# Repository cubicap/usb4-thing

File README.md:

# USB4 Thing

An attemt at creating a USB4 multiplexer controlled by ESP32-S3.

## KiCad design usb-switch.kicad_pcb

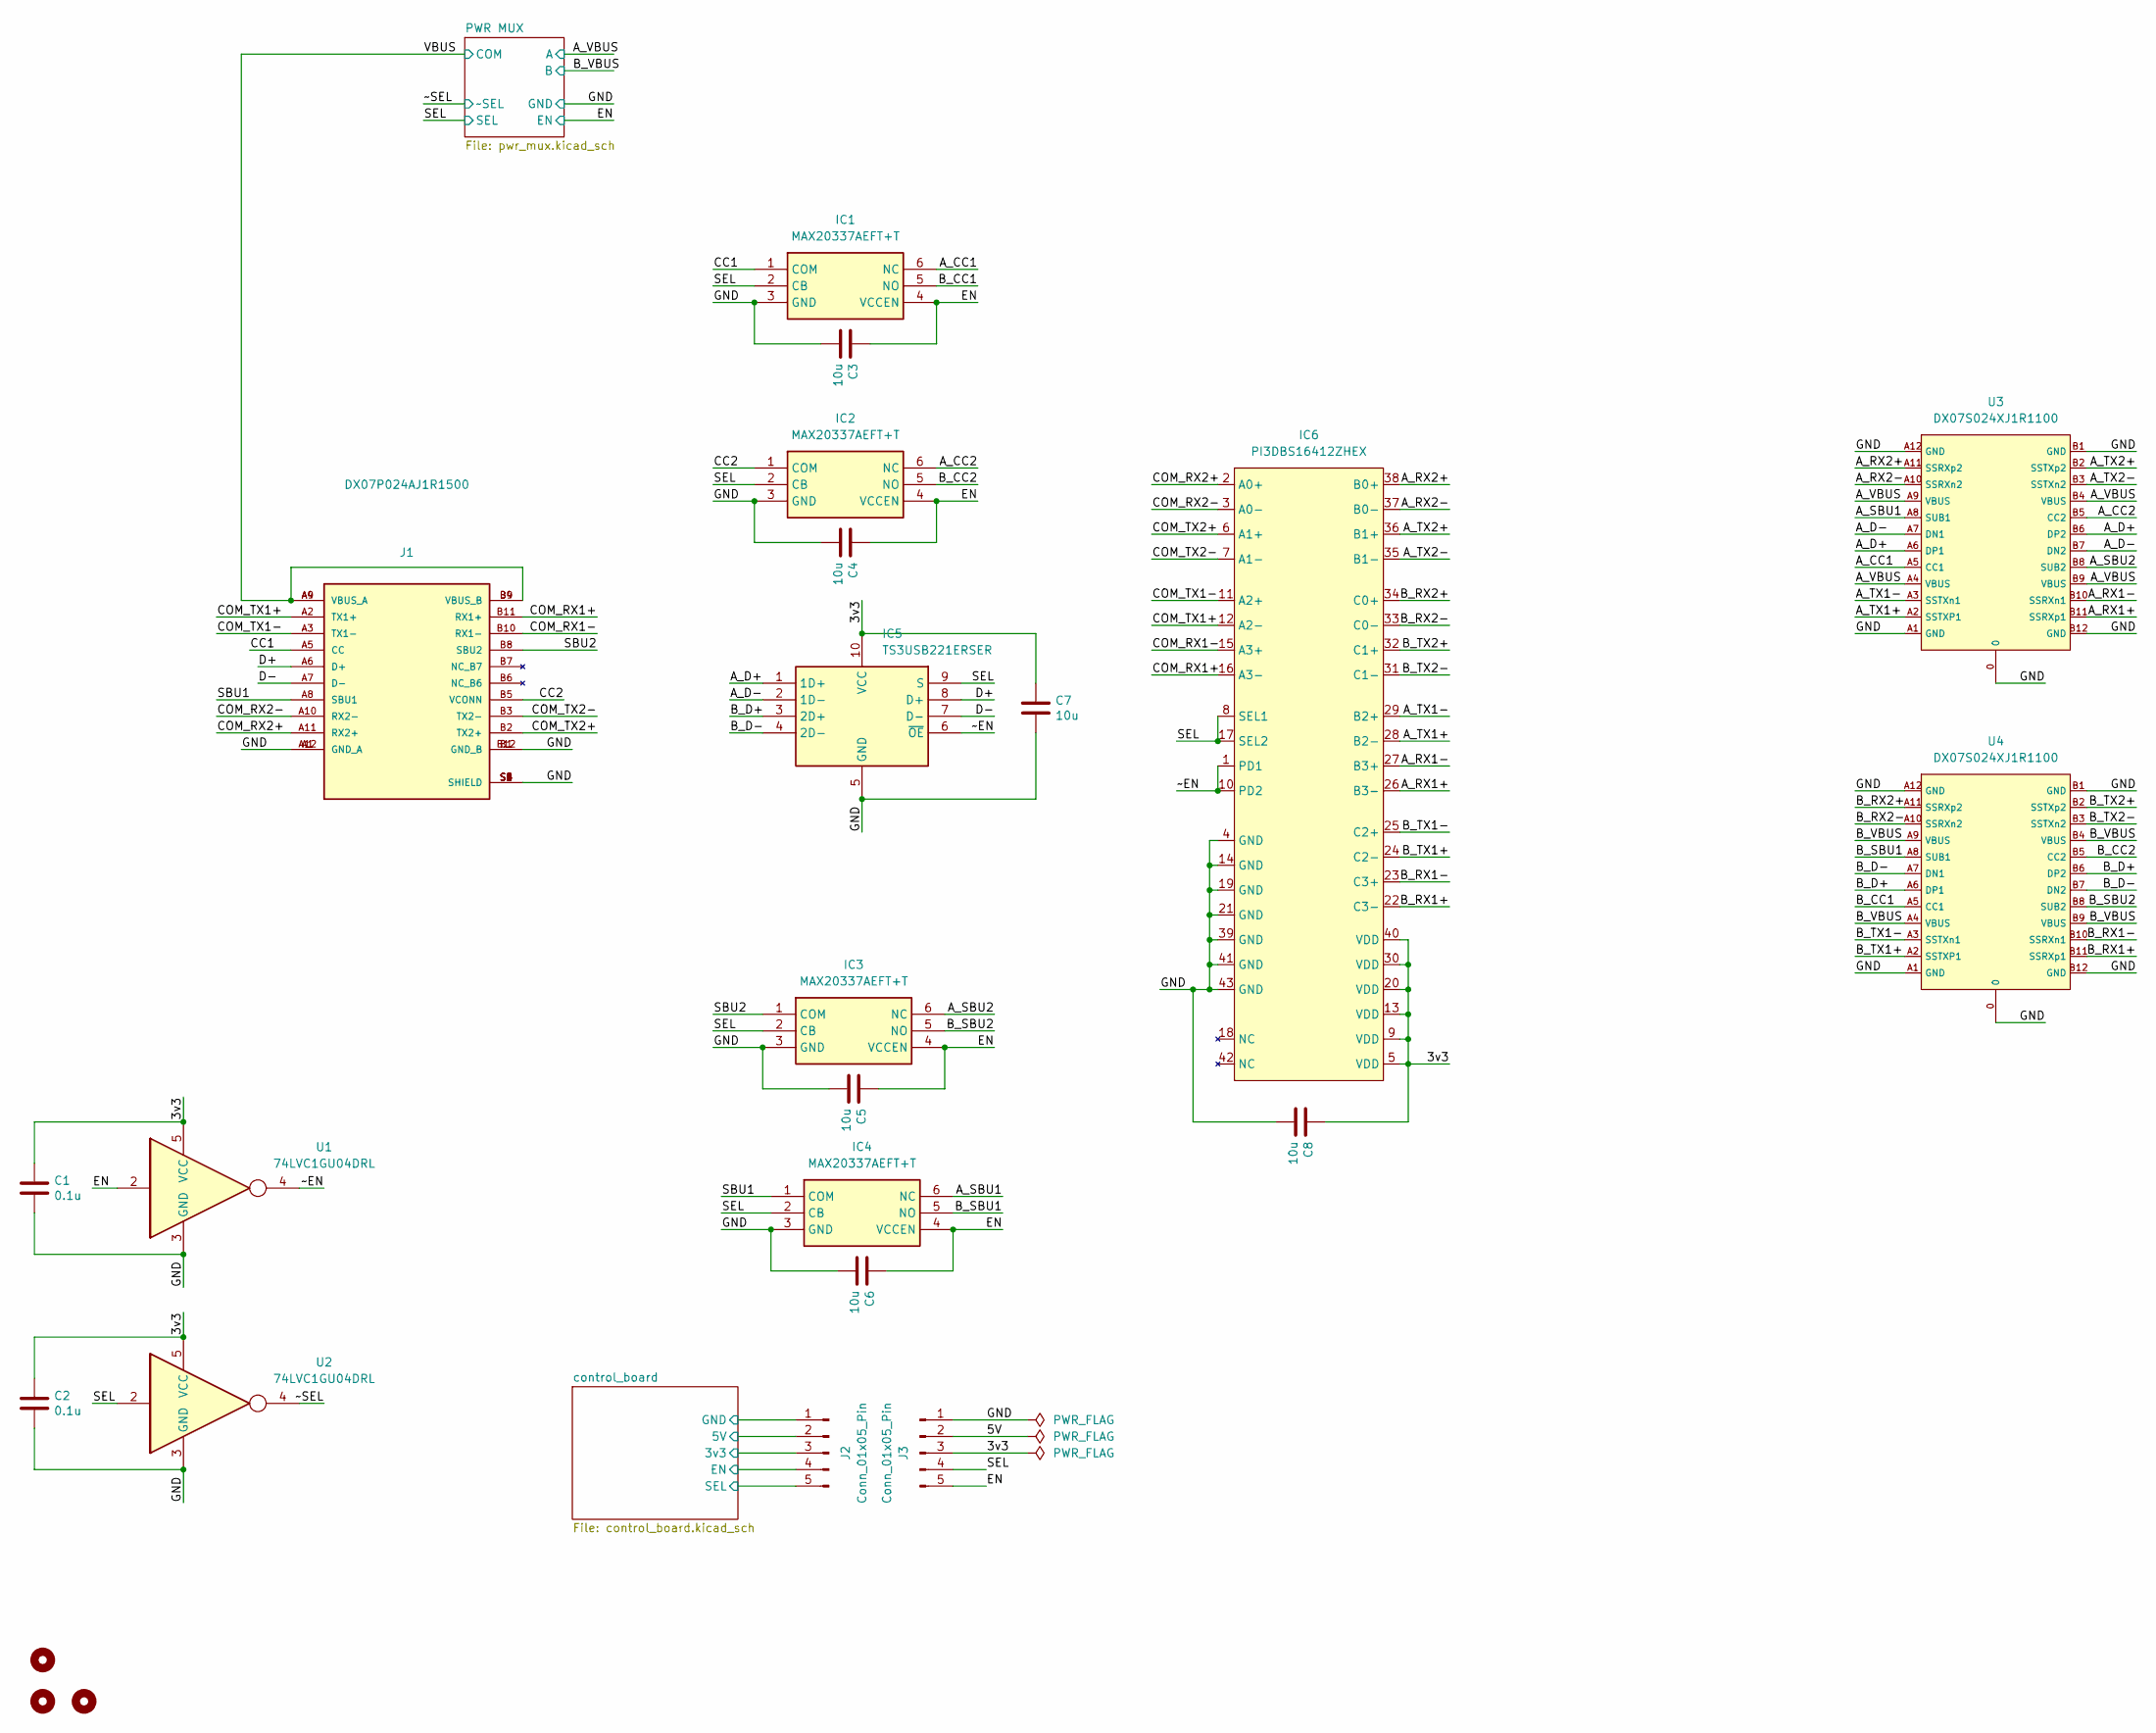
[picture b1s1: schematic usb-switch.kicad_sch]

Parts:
C1, C2: 0.1u; C_0402_1005Metric; LCSC C15525
C3, C4, C5, C6, C7, C8: 10u; C_0402_1005Metric; LCSC C15525
H1, H2, H3: MountingHole; MountingHole_3mm
IC1, IC2, IC3, IC4: MAX20337AEFT+T; SON50P125X175X60-6N; Mouser Part Number 700-MAX20337AEFT+T
IC5: TS3USB221ERSER; Mouser Part Number 595-TS3USB221ERSER
IC6: PI3DBS16412ZHEX; WQFN-42-1EP_3.5x9mm_P0.5mm_EP2.05x7.55mm
J1: DX07P024AJ1R1500; JAE_DX07P024AJ1R1500; PARTREV January 2016
J2, J3: Conn_01x05_Pin; PinHeader_1x05_P2.54mm_Vertical
U1, U2: 74LVC1GU04DRL; SOT-553
U3, U4: DX07S024XJ1R1100; USB-C-TH_DX07S024XJ1R1100-1; LCSC C134113

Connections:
/3v3: C1.1, C2.1, C7.1, C8.1, IC5.10 (VCC), IC6.5 (VDD), IC6.9 (VDD), IC6.13 (VDD), IC6.20 (VDD), IC6.30 (VDD), IC6.40 (VDD), J3.3, U1.5 (VCC), U2.5 (VCC)
/5V: J3.2
/A_CC1: IC1.6 (NC), U3.A5 (CC1)
/A_CC2: IC2.6 (NC), U3.B5 (CC2)
/A_D+: IC5.1 (1D+), U3.A6 (DP1), U3.B6 (DP2)
/A_D-: IC5.2 (1D-), U3.A7 (DN1), U3.B7 (DN2)
/A_RX1+: IC6.26 (B3-), U3.B11 (SSRXp1)
/A_RX1-: IC6.27 (B3+), U3.B10 (SSRXn1)
/A_RX2+: IC6.38 (B0+), U3.A11 (SSRXp2)
/A_RX2-: IC6.37 (B0-), U3.A10 (SSRXn2)
/A_SBU1: IC4.6 (NC), U3.A8 (SUB1)
/A_SBU2: IC3.6 (NC), U3.B8 (SUB2)
/A_TX1+: IC6.28 (B2-), U3.A2 (SSTXP1)
/A_TX1-: IC6.29 (B2+), U3.A3 (SSTXn1)
/A_TX2+: IC6.36 (B1+), U3.B2 (SSTXp2)
/A_TX2-: IC6.35 (B1-), U3.B3 (SSTXn2)
/A_VBUS: U3.A4 (VBUS), U3.A9 (VBUS), U3.B4 (VBUS), U3.B9 (VBUS); also elsewhere on the board
/B_CC1: IC1.5 (NO), U4.A5 (CC1)
/B_CC2: IC2.5 (NO), U4.B5 (CC2)
/B_D+: IC5.3 (2D+), U4.A6 (DP1), U4.B6 (DP2)
/B_D-: IC5.4 (2D-), U4.A7 (DN1), U4.B7 (DN2)
/B_RX1+: IC6.22 (C3-), U4.B11 (SSRXp1)
/B_RX1-: IC6.23 (C3+), U4.B10 (SSRXn1)
/B_RX2+: IC6.34 (C0+), U4.A11 (SSRXp2)
/B_RX2-: IC6.33 (C0-), U4.A10 (SSRXn2)
/B_SBU1: IC4.5 (NO), U4.A8 (SUB1)
/B_SBU2: IC3.5 (NO), U4.B8 (SUB2)
/B_TX1+: IC6.24 (C2-), U4.A2 (SSTXP1)
/B_TX1-: IC6.25 (C2+), U4.A3 (SSTXn1)
/B_TX2+: IC6.32 (C1+), U4.B2 (SSTXp2)
/B_TX2-: IC6.31 (C1-), U4.B3 (SSTXn2)
/B_VBUS: U4.A4 (VBUS), U4.A9 (VBUS), U4.B4 (VBUS), U4.B9 (VBUS); also elsewhere on the board
/CC1: IC1.1 (COM), J1.A5 (CC)
/CC2: IC2.1 (COM), J1.B5 (VCONN)
/COM_RX1+: IC6.16 (A3-), J1.B11 (RX1+)
/COM_RX1-: IC6.15 (A3+), J1.B10 (RX1-)
/COM_RX2+: IC6.2 (A0+), J1.A11 (RX2+)
/COM_RX2-: IC6.3 (A0-), J1.A10 (RX2-)
/COM_TX1+: IC6.12 (A2-), J1.A2 (TX1+)
/COM_TX1-: IC6.11 (A2+), J1.A3 (TX1-)
/COM_TX2+: IC6.6 (A1+), J1.B2 (TX2+)
/COM_TX2-: IC6.7 (A1-), J1.B3 (TX2-)
/D+: IC5.8 (D+), J1.A6 (D+)
/D-: IC5.7 (D-), J1.A7 (D-)
/EN: C3.1, C4.1, C5.1, C6.1, IC1.4 (VCCEN), IC2.4 (VCCEN), IC3.4 (VCCEN), IC4.4 (VCCEN), J3.5, U1.2; also elsewhere on the board
/GND: C1.2, C2.2, C3.2, C4.2, C5.2, C6.2, C7.2, C8.2, IC1.3 (GND), IC2.3 (GND), IC3.3 (GND), IC4.3 (GND), IC5.5 (GND), IC6.4 (GND), IC6.14 (GND), IC6.19 (GND), IC6.21 (GND), IC6.39 (GND), IC6.41 (GND), IC6.43 (GND), J1.A1 (GND_A), J1.A12 (GND_A), J1.B1 (GND_B), J1.B12 (GND_B), J1.S1 (SHIELD), J1.S2 (SHIELD), J1.S3 (SHIELD), J1.S4 (SHIELD), J1.S5 (SHIELD), J1.S6 (SHIELD), J3.1, U1.3 (GND), U2.3 (GND), U3.0, U3.A1 (GND), U3.A12 (GND), U3.B1 (GND), U3.B12 (GND), U4.0, U4.A1 (GND), U4.A12 (GND), U4.B1 (GND), U4.B12 (GND); also elsewhere on the board
/SBU1: IC4.1 (COM), J1.A8 (SBU1)
/SBU2: IC3.1 (COM), J1.B8 (SBU2)
/SEL: IC1.2 (CB), IC2.2 (CB), IC3.2 (CB), IC4.2 (CB), IC5.9 (S), IC6.8 (SEL1), IC6.17 (SEL2), J3.4, U2.2; also elsewhere on the board
/VBUS: J1.A4 (VBUS_A), J1.A9 (VBUS_A), J1.B4 (VBUS_B), J1.B9 (VBUS_B); also elsewhere on the board
/control_board/3v3: J2.3; also elsewhere on the board
/control_board/5V: J2.2; also elsewhere on the board
/control_board/EN: J2.4; also elsewhere on the board
/control_board/GND: J2.1; also elsewhere on the board
/control_board/SEL: J2.5; also elsewhere on the board
/~EN: IC5.6 (~OE), IC6.1 (PD1), IC6.10 (PD2), U1.4
/~SEL: U2.4; also elsewhere on the board

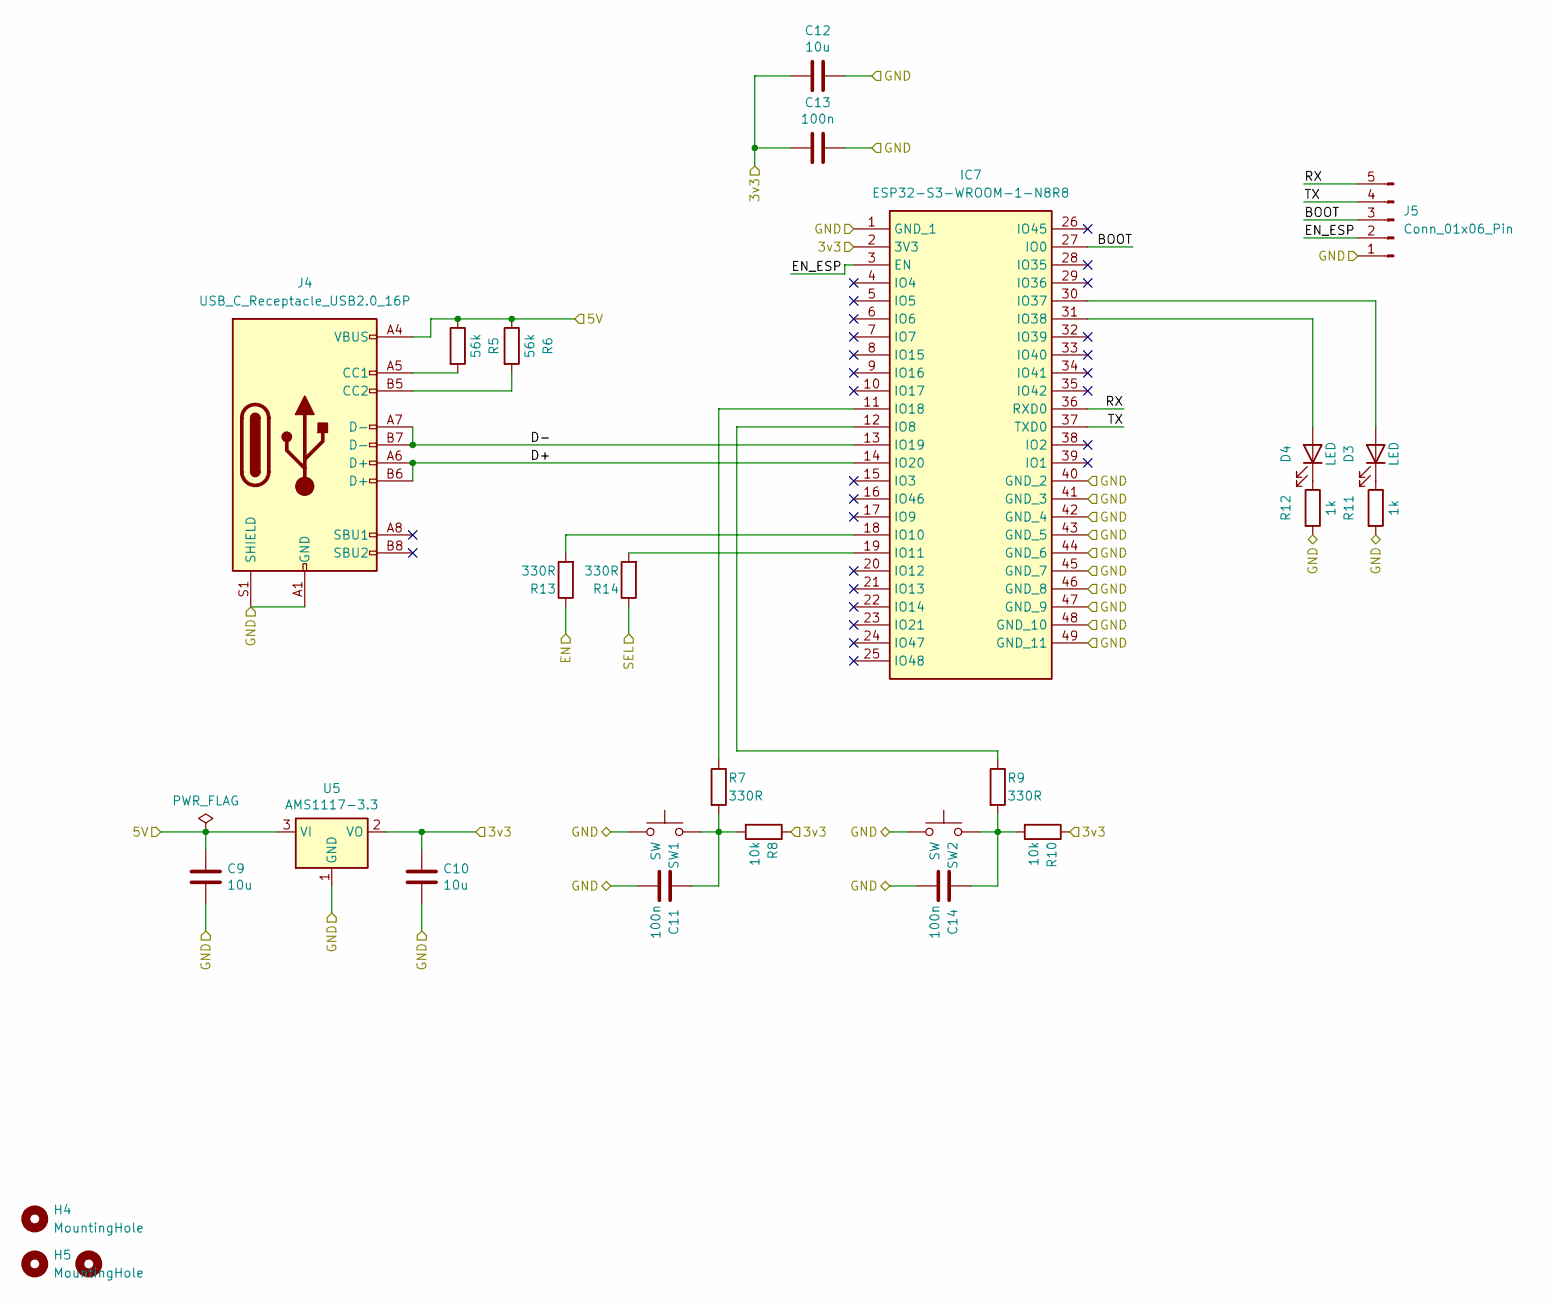
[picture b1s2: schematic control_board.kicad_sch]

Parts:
C9, C10, C12: 10u; C_0402_1005Metric; LCSC C15525
C11, C13, C14: 100n; C_0402_1005Metric; LCSC C1525
D3, D4: LED; LED_0603_1608Metric; LCSC C965799
H4, H5, H6: MountingHole; MountingHole_3mm
IC7: ESP32-S3-WROOM-1-N8R8; ESP32S3WROOM1N8R8; Mouser Part Number 356-EP32S3WROOM1N8R8
J4: USB_C_Receptacle_USB2.0_16P; USB_C_Receptacle_GCT_USB4105-xx-A_16P_TopMnt_Horizontal
J5: Conn_01x06_Pin; PinHeader_1x05_P2.54mm_Horizontal
R5, R6: 56k; R_0402_1005Metric
R7, R9, R13, R14: 330R; R_0402_1005Metric; LCSC C25744
R8, R10: 10k; R_0402_1005Metric; LCSC C25744
R11, R12: 1k; R_0402_1005Metric; LCSC C11702
SW1, SW2: SW; SW_Push_1P1T_NO_Vertical_Wuerth_434133025816; LCSC C127488
U5: AMS1117-3.3; SOT-223-3_TabPin2; JLCPCB_CORRECTION 0;0;180

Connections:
/control_board/3v3: C10.1, C12.2, C13.2, IC7.2 (3V3), R8.1, R10.1, U5.2 (VO); also elsewhere on the board
/control_board/5V: C9.1, J4.A4 (VBUS), J4.A9 (VBUS), J4.B4 (VBUS), J4.B9 (VBUS), R5.1, R6.1, U5.3 (VI); also elsewhere on the board
/control_board/BOOT: IC7.27 (IO0), J5.3
/control_board/D+: IC7.14 (IO20), J4.A6 (D+), J4.B6 (D+)
/control_board/D-: IC7.13 (IO19), J4.A7 (D-), J4.B7 (D-)
/control_board/EN: R13.1; also elsewhere on the board
/control_board/EN_ESP: IC7.3 (EN), J5.2
/control_board/GND: C9.2, C10.2, C11.2, C12.1, C13.1, C14.2, IC7.1 (GND_1), IC7.40 (GND_2), IC7.41 (GND_3), IC7.42 (GND_4), IC7.43 (GND_5), IC7.44 (GND_6), IC7.45 (GND_7), IC7.46 (GND_8), IC7.47 (GND_9), IC7.48 (GND_10), IC7.49 (GND_11), J4.A1 (GND), J4.A12 (GND), J4.B1 (GND), J4.B12 (GND), J4.S1 (SHIELD), J5.1, R11.2, R12.2, SW1.1, SW2.1, U5.1 (GND); also elsewhere on the board
/control_board/RX: IC7.36 (RXD0), J5.5
/control_board/SEL: R14.1; also elsewhere on the board
/control_board/TX: IC7.37 (TXD0), J5.4
unnamed: C11.1, R7.2, R8.2, SW1.2
unnamed: C14.1, R9.2, R10.2, SW2.2
unnamed: D3.2 (A), IC7.31 (IO38)
unnamed: D3.1 (K), R11.1
unnamed: D4.2 (A), IC7.30 (IO37)
unnamed: D4.1 (K), R12.1
unnamed: IC7.12 (IO8), R9.1
unnamed: IC7.18 (IO10), R13.2
unnamed: IC7.19 (IO11), R14.2
unnamed: IC7.11 (IO18), R7.1
unnamed: J4.A5 (CC1), R5.2
unnamed: J4.B5 (CC2), R6.2

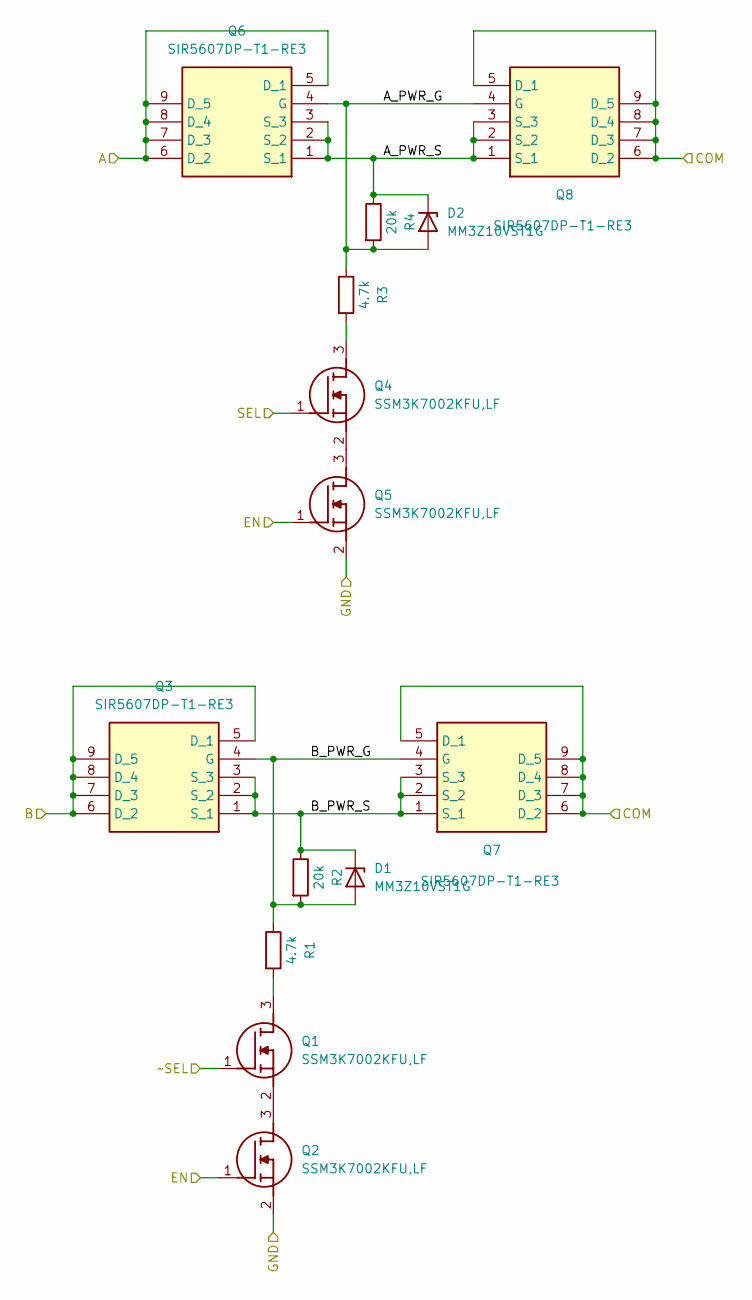
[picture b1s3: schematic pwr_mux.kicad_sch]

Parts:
D1, D2: MM3Z10VST1G; D_SOD-323
Q1, Q2, Q4, Q5: SSM3K7002KFU,LF; SSM3K7002CFULF; Mouser Part Number 757-SSM3K7002KFULF
Q3, Q6, Q7, Q8: SIR5607DP-T1-RE3; SIR681DPT1RE3
R1, R3: 4.7k; R_0402_1005Metric
R2, R4: 20k; R_0402_1005Metric

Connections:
/A_VBUS: Q6.5 (D_1), Q6.6 (D_2), Q6.7 (D_3), Q6.8 (D_4), Q6.9 (D_5); also elsewhere on the board
/B_VBUS: Q3.5 (D_1), Q3.6 (D_2), Q3.7 (D_3), Q3.8 (D_4), Q3.9 (D_5); also elsewhere on the board
/EN: Q2.1 (G), Q5.1 (G); also elsewhere on the board
/GND: Q2.2 (S), Q5.2 (S); also elsewhere on the board
/PWR MUX/A_PWR_G: D2.2 (A), Q6.4 (G), Q8.4 (G), R3.1, R4.2
/PWR MUX/A_PWR_S: D2.1 (K), Q6.1 (S_1), Q6.2 (S_2), Q6.3 (S_3), Q8.1 (S_1), Q8.2 (S_2), Q8.3 (S_3), R4.1
/PWR MUX/B_PWR_G: D1.2 (A), Q3.4 (G), Q7.4 (G), R1.1, R2.2
/PWR MUX/B_PWR_S: D1.1 (K), Q3.1 (S_1), Q3.2 (S_2), Q3.3 (S_3), Q7.1 (S_1), Q7.2 (S_2), Q7.3 (S_3), R2.1
/SEL: Q4.1 (G); also elsewhere on the board
/VBUS: Q7.5 (D_1), Q7.6 (D_2), Q7.7 (D_3), Q7.8 (D_4), Q7.9 (D_5), Q8.5 (D_1), Q8.6 (D_2), Q8.7 (D_3), Q8.8 (D_4), Q8.9 (D_5); also elsewhere on the board
/~SEL: Q1.1 (G); also elsewhere on the board
unnamed: Q1.3 (D), R1.2
unnamed: Q1.2 (S), Q2.3 (D)
unnamed: Q4.3 (D), R3.2
unnamed: Q4.2 (S), Q5.3 (D)

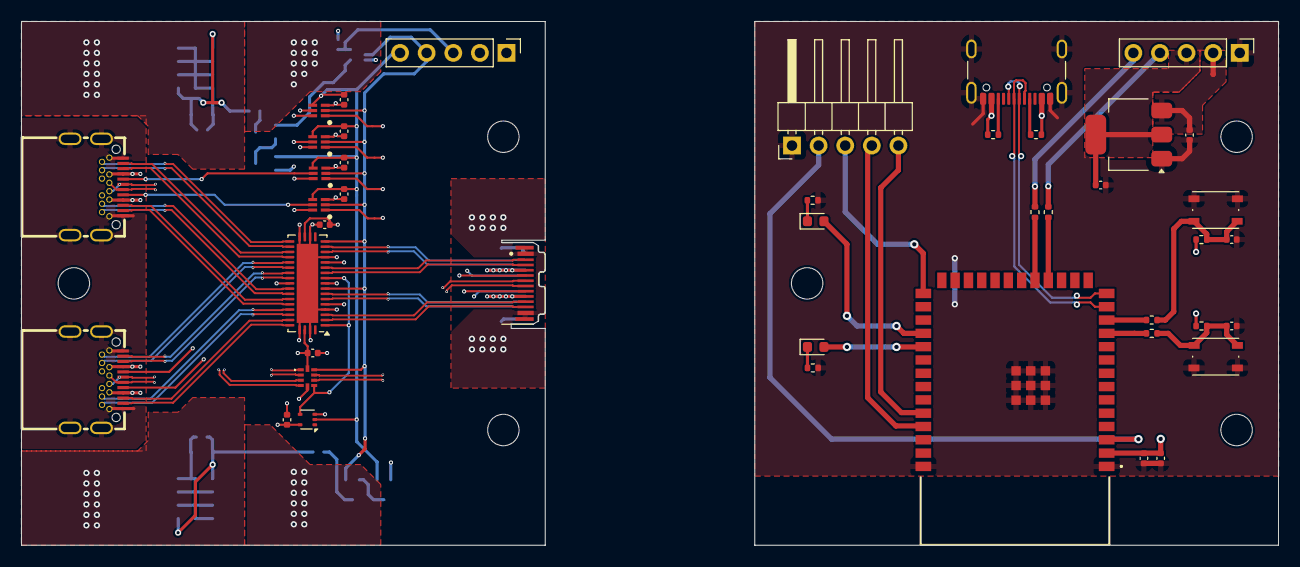
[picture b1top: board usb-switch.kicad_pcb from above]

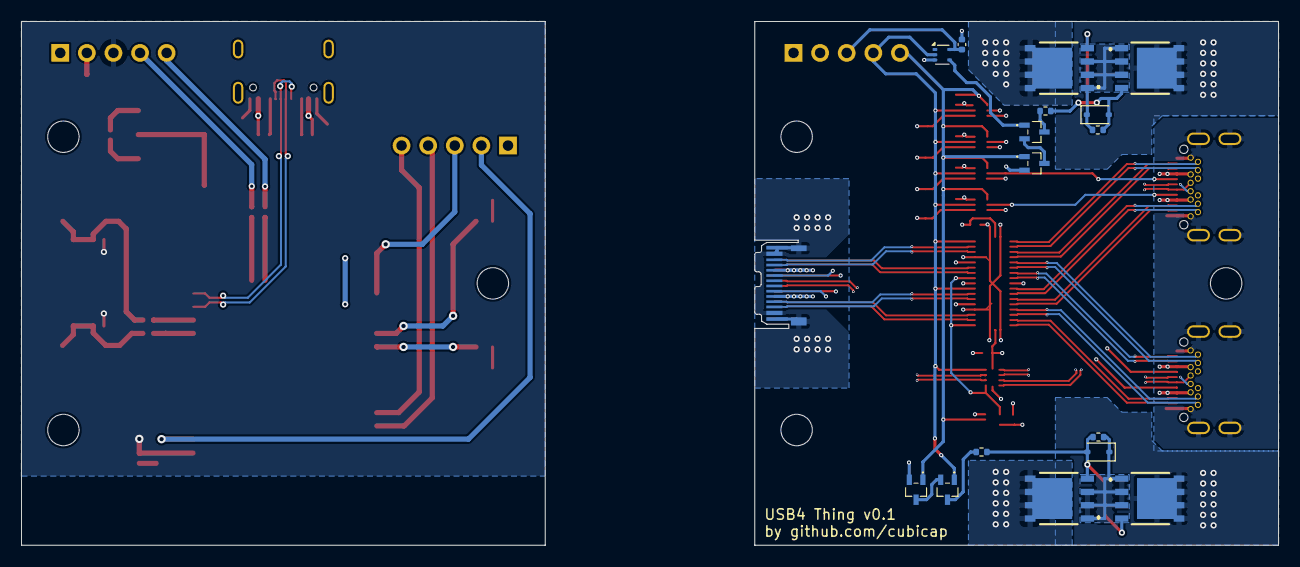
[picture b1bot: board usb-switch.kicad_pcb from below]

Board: 6 copper layers, 120.0 x 50.0 mm, 65 parts (16 on the bottom side), 82 nets.

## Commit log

2024-06-15 initial upload
2024-06-15 add capacitors, move B pwr control, select remaining components
2024-06-16 fix usb connections, board dimensions
2024-06-17 fixes
